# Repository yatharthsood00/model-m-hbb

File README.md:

# Model M Controller, by HBB

This is a drop-in replacement controller for the IBM Model M with QMK and VIAL support. I designed this for myself, and my own Models M, as well as some that I have sold/gifted to friends in the custom keyboard community, which is why this is designed only for the Models M that I own (the 101 key ANSI version, and the Space Saving Keyboard).

**Status (01-02-2026):** PCBA produced via JLCPCB and delivered. Tested successfully for basic operation. JST connector assembly in progress (I don't have a hot air soldering station).

## TODO:

1. Testing status lights and buzzer operation.
2. Uploading QMK and VIAL source to their respective repos.
3. BOM list availability in README (this file).
4. Fitment issue resolution due to USB-C port being too low for the existing cutout.
5. Figuring out solenoid operation and components required.
6. Pictures.

## Specs

- Based on the STM32F072CBT6 microcontroller, wide availability and great pedigree with QMK and VIAL. Works over USB-C.
- Like said, QMK and VIAL compatibility (firmware push and merge pending but it'll be there).
- Buzzer and Solenoid compatibility (optional, WIP). The exact parts needed for the solenoid are TBD and testing is required to be done first.
- Custom Status Lights PCB for adding LEDs in the colours of your choosing (standard DIP LEDs only), for the variants that have the possibility of adding such lights.
- Compatible with the 101-key and SSK Models M, Terminal or PS/2, both ANSI and ISO* versions.

*I need help with the firmware, as I don't own an ISO Model M to test it on.

## Why a new controller?

The "replacement Model M Controller" idea has already been implemented by many projects, with them already doing the work on understanding how the controller can be made in the first place, and the dimensions of a board that will fit the space voided by the original controller, that would be necessary to know how to place the components on my replacement. With that in mind, I would like to specifically highlight the [Ctrl-M](https://github.com/nuess0r/ctrl-M) and the [Model H](https://github.com/jhawthorn/modelh) projects, as they both provided me a sanity check of the dimensions of the PCB that I needed to design, separate from my own measurements of the several OEM controllers I now own.

While the above two are perfectly capable equivalents of my own creation, and I'm sure many would find either more suited for their own use cases, I found some limitations with the both of them that were disqualifying for my own use. Here is what I needed:

1. USB-C. All my other keyboards work off the same USB-C cable that I can detach from the keyboard end and swap the keyboard on my desk with another. While the Model H had this ability with the right Pro Micro controller, the Ctrl-M did not.
2. PCBA. It's significantly more expensive to produce this PCB via JLCPCB, with or without their assembly service. It's also almost conventional to expect a vintage keyboard replacement part to use a more "period-accurate" part selection, with through-hole componentry wherever possible, but I wanted something more modern that resembled a keyboard PCB you would get with a custom keyboard today. An entirely vain addition.
3. Additional bells and whistles. A keyboard with a solenoid is something I always wanted to add to my collection. While there are modern boards that will provide that to you, they are superseded, in my opinion, by a roomy plastic chassis, from a time when keyboards were normally significantly louer. Neither of the existing modules could provide that to me without a significant modification, so I decided to start from scratch.

Note: As a starting point for the solenoid and buzzer, I took directly from the [M122ion Control](https://github.com/dcpedit/mission-control) project, although the end result will use different components for the switching circuit.

All the above are fulfilled by this controller. This is also my first PCB design, and I enjoyed working on it. 

**As a disclaimer, however,** I don't claim this to be an extremely competent component, and I would advise anyone thinking of ordering a production run of this PCB to do their due diligence first. This is a hobbyist project first of all. Nonetheless, don't hesitate to reach out to me on @hardbodybrain on Discord, or on my personal email ID, yatharthsood00 [at] gmail [dot] com for any questions or clarifications, as well as if you want to share your experiences with this PCB, if you chose to get one of your own!

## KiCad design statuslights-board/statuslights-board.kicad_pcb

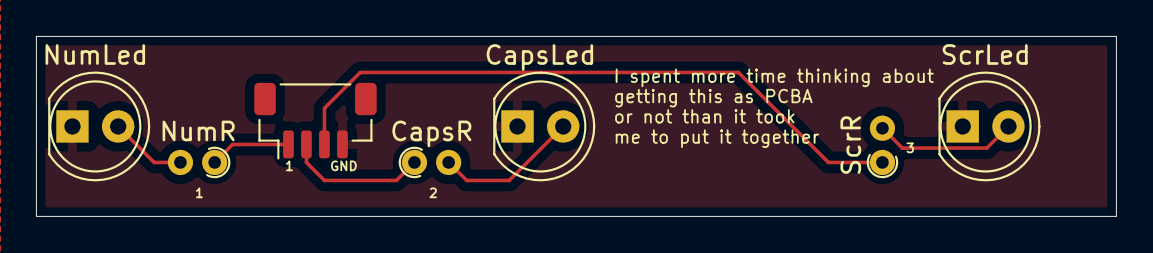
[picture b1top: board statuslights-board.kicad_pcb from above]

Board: 2 copper layers, 60.0 x 10.0 mm, 7 parts (0 on the bottom side), 7 nets.

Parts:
CapsLed: LED; LED_D5.0mm
CapsR: 51R; R_Axial_DIN0204_L3.6mm_D1.6mm_P1.90mm_Vertical
J1: JST SH (from controller); JST_SH_BM04B-SRSS-TB_1x04-1MP_P1.00mm_Vertical
NumLed: LED; LED_D5.0mm
NumR: 51R; R_Axial_DIN0204_L3.6mm_D1.6mm_P1.90mm_Vertical
ScrLed: LED; LED_D5.0mm
ScrR: 51R; R_Axial_DIN0204_L3.6mm_D1.6mm_P1.90mm_Vertical

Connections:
CapsLk: CapsR.1, J1.2
GND: CapsLed.1 (K), J1.4, NumLed.1 (K), ScrLed.1 (K)
unnamed: CapsLed.2 (A), CapsR.2
unnamed: NumLed.2 (A), NumR.2
unnamed: ScrLed.2 (A), ScrR.2
NumLk: J1.1, NumR.1
ScrLk: J1.3, ScrR.1

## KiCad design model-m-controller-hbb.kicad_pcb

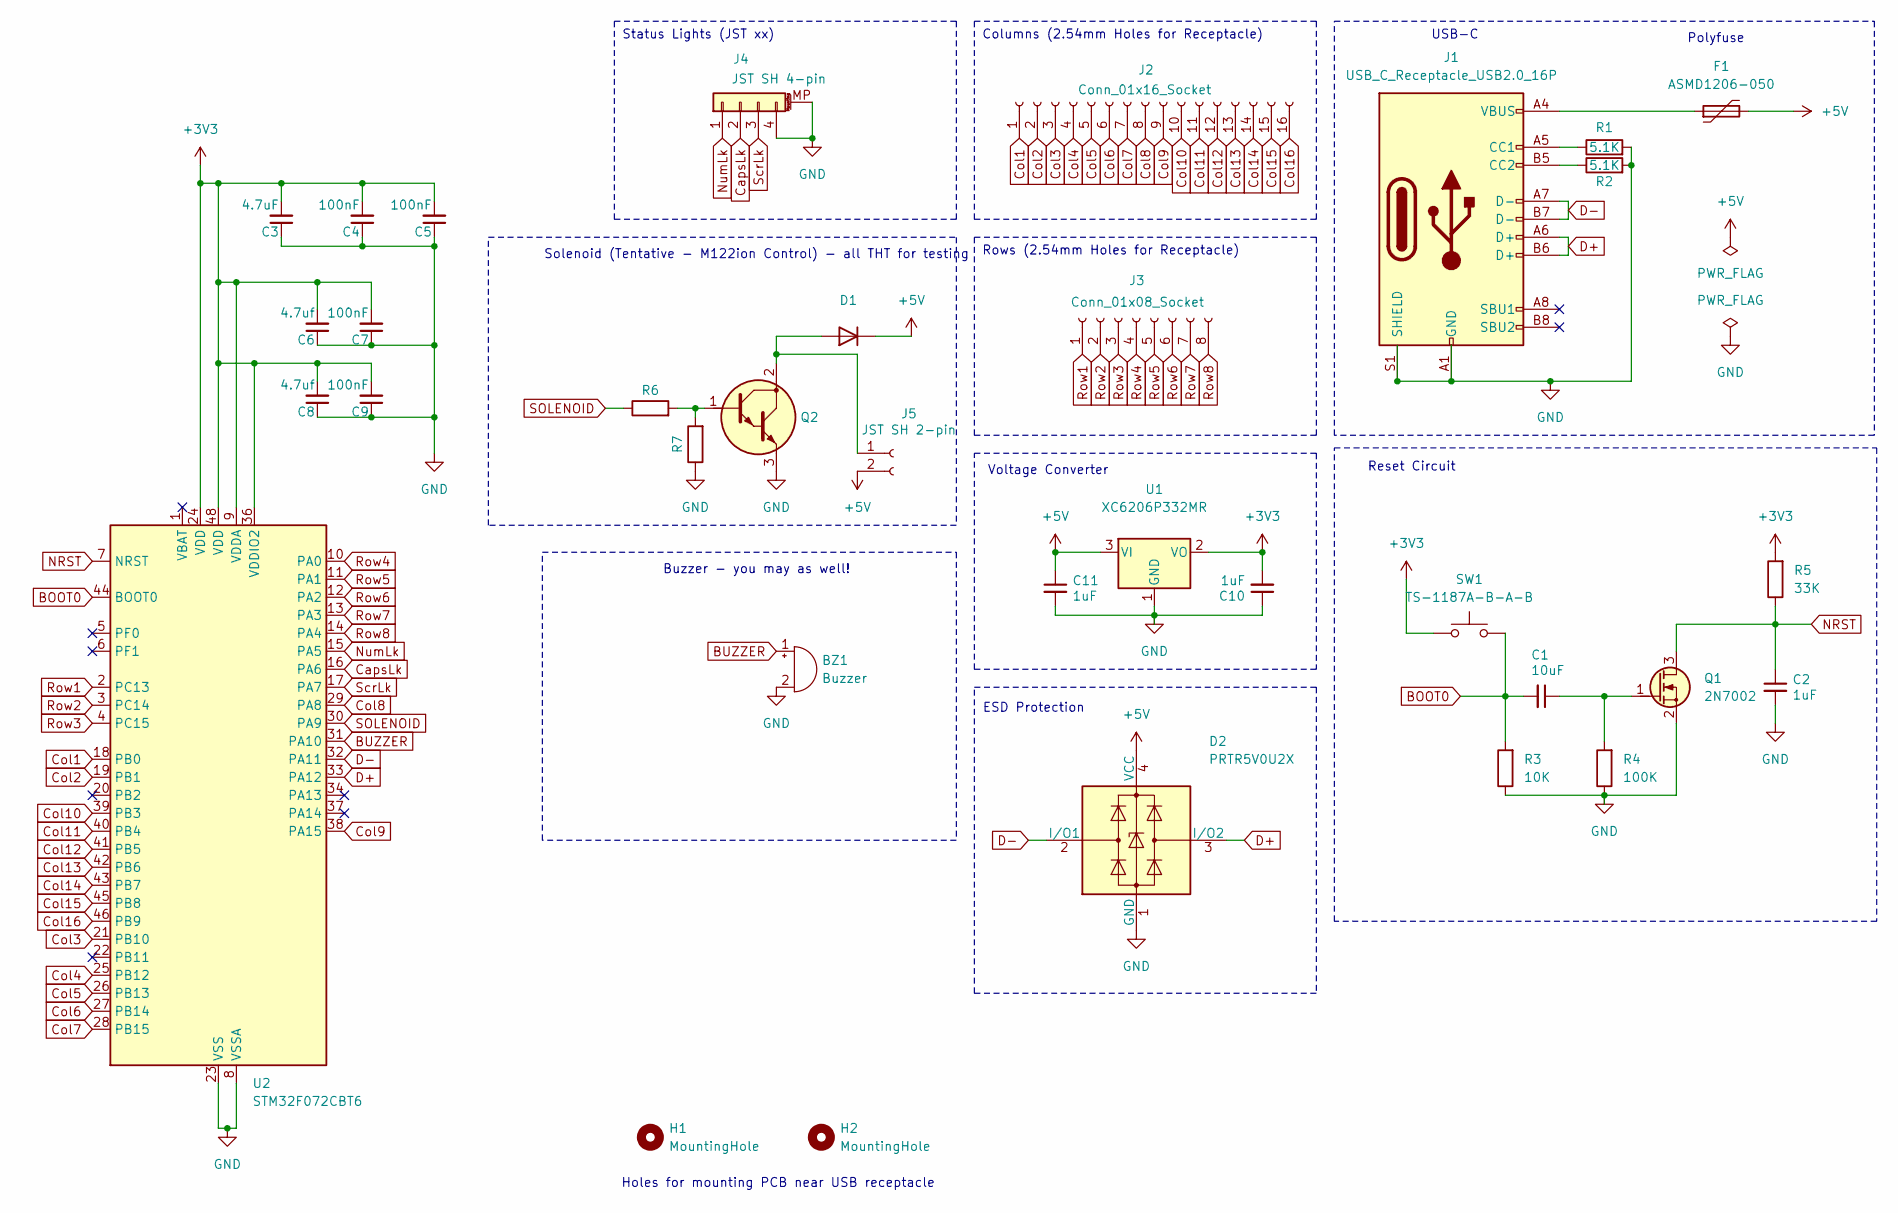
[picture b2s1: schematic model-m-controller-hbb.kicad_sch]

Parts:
BZ1: Buzzer; Buzzer_12x9.5RM7.6
C1: 10uF; C_0402_1005Metric; MPN CL05A105KA5NQNC; LCSC C52923
C2, C10, C11: 1uF; C_0402_1005Metric; MPN CL05A105KA5NQNC; LCSC C52923
C3: 4.7uF; C_0402_1005Metric
C4, C5, C7, C9: 100nF; C_0402_1005Metric
C6, C8: 4.7uf; C_0402_1005Metric
D1: D_DO-41_SOD81_P2.54mm_Vertical_AnodeUp
D2: PRTR5V0U2X; SOT-143; MPN PRTR5V0U2X
F1: ASMD1206-050; Fuse_1206_3216Metric
H1, H2: MountingHole; MountingHole_4mm
J1: USB_C_Receptacle_USB2.0_16P; USB_C_Receptacle_HRO_TYPE-C-31-M-12
J2: Conn_01x16_Socket; PinHeader_1x16_P2.54mm_Vertical
J3: Conn_01x08_Socket; PinHeader_1x08_P2.54mm_Vertical
J4: JST SH 4-pin; JST_SH_BM04B-SRSS-TB_1x04-1MP_P1.00mm_Vertical
J5: JST SH 2-pin; JST_SH_BM02B-SRSS-TB_1x02-1MP_P1.00mm_Vertical
Q1: 2N7002; SOT-23
Q2: TO-220-3_Vertical_BCE
R1, R2: 5.1K; R_0402_1005Metric
R3: 10K; R_0402_1005Metric
R4: 100K; R_0402_1005Metric
R5: 33K; R_0402_1005Metric
R6, R7: R_Axial_DIN0204_L3.6mm_D1.6mm_P1.90mm_Vertical
SW1: TS-1187A-B-A-B; SW_Push_1P1T_XKB_TS-1187A
U1: XC6206P332MR; SOT-23; MPN XC6206P332MR-G
U2: STM32F072CBT6; LQFP-48_7x7mm_P0.5mm

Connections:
+3V3: C3.2, C4.2, C5.2, C6.2, C7.2, C8.2, C9.2, C10.2, R5.2, SW1.1, U1.2 (VO), U2.9 (VDDA), U2.24 (VDD), U2.36 (VDDIO2), U2.48 (VDD)
+5V: C11.1, D1.1 (K), D2.4 (VCC), F1.2, J5.2, U1.3 (VI)
BOOT0: C1.2, R3.2, SW1.2, U2.44 (BOOT0)
BUZZER: BZ1.1 (+), U2.31 (PA10)
CapsLk: J4.2, U2.16 (PA6)
Col1: J2.1, U2.18 (PB0)
Col2: J2.2, U2.19 (PB1)
Col3: J2.3, U2.21 (PB10)
Col4: J2.4, U2.25 (PB12)
Col5: J2.5, U2.26 (PB13)
Col6: J2.6, U2.27 (PB14)
Col7: J2.7, U2.28 (PB15)
Col8: J2.8, U2.29 (PA8)
Col9: J2.9, U2.38 (PA15)
Col10: J2.10, U2.39 (PB3)
Col11: J2.11, U2.40 (PB4)
Col12: J2.12, U2.41 (PB5)
Col13: J2.13, U2.42 (PB6)
Col14: J2.14, U2.43 (PB7)
Col15: J2.15, U2.45 (PB8)
Col16: J2.16, U2.46 (PB9)
D+: D2.3 (I/O2), J1.A6 (D+), J1.B6 (D+), U2.33 (PA12)
D-: D2.2 (I/O1), J1.A7 (D-), J1.B7 (D-), U2.32 (PA11)
GND: BZ1.2 (-), C2.2, C3.1, C4.1, C5.1, C6.1, C7.1, C8.1, C9.1, C10.1, C11.2, D2.1 (GND), J1.A1 (GND), J1.A12 (GND), J1.B1 (GND), J1.B12 (GND), J1.S1 (SHIELD), J4.4, J4.MP (MountPin), Q1.2 (S), Q2.3 (E), R1.2, R2.2, R3.1, R4.1, R7.1, U1.1 (GND), U2.8 (VSSA), U2.23 (VSS), U2.35 (VSS), U2.47 (VSS)
NRST: C2.1, Q1.3 (D), R5.1, U2.7 (NRST)
unnamed: D1.2 (A), J5.1, Q2.2 (C)
unnamed: F1.1, J1.A4 (VBUS), J1.A9 (VBUS), J1.B4 (VBUS), J1.B9 (VBUS)
unnamed: J1.A5 (CC1), R1.1
unnamed: J1.B5 (CC2), R2.1
unnamed: C1.1, Q1.1 (G), R4.2
unnamed: Q2.1 (B), R6.2, R7.2
NumLk: J4.1, U2.15 (PA5)
Row1: J3.1, U2.2 (PC13)
Row2: J3.2, U2.3 (PC14)
Row3: J3.3, U2.4 (PC15)
Row4: J3.4, U2.10 (PA0)
Row5: J3.5, U2.11 (PA1)
Row6: J3.6, U2.12 (PA2)
Row7: J3.7, U2.13 (PA3)
Row8: J3.8, U2.14 (PA4)
SOLENOID: R6.1, U2.30 (PA9)
ScrLk: J4.3, U2.17 (PA7)

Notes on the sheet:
Columns (2.54mm Holes for Receptacle)
Status Lights (JST xx)
Rows (2.54mm Holes for Receptacle)
Holes for mounting PCB near USB receptacle
Polyfuse
Voltage Converter
ESD Protection
Reset Circuit
Solenoid (Tentative - M122ion Control) - all THT for testing
USB-C
Buzzer - you may as well!

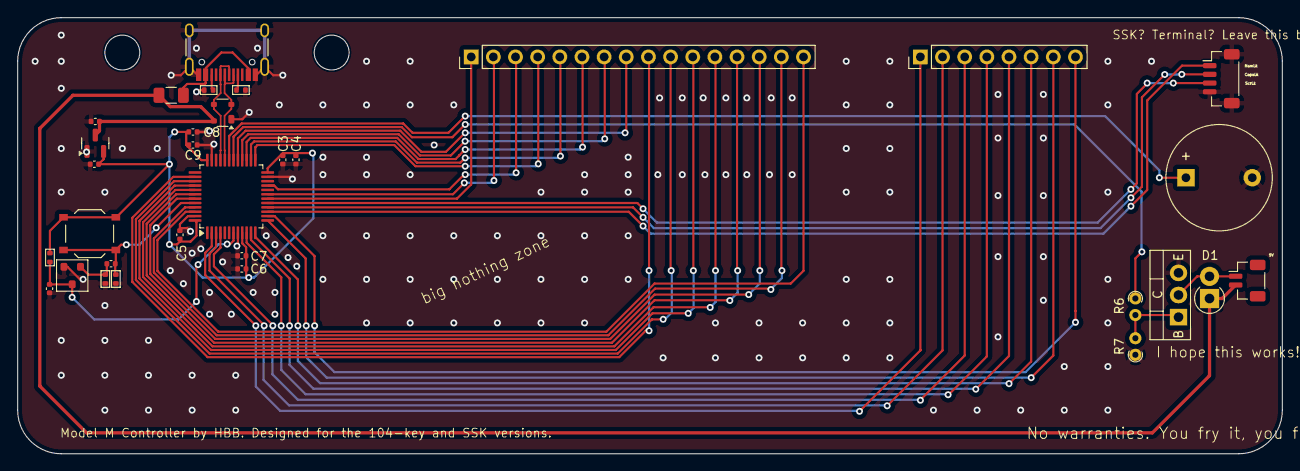
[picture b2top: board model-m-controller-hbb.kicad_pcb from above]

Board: 2 copper layers, 145.0 x 50.0 mm, 34 parts (0 on the bottom side), 42 nets.

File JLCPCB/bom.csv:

Designator,Footprint,Quantity,Value,LCSC Part #
BZ1,Buzzer_12x9.5RM7.6,1,Buzzer,
C1,0402,1,10uF,C52923
"C10, C11, C2",0402,3,1uF,C52923
"C3, C6, C8",0402,3,4.7uF,
"C4, C5, C7, C9",0402,4,100nF,
D1,D_DO-41_SOD81_P2.54mm_Vertical_AnodeUp,1,~,
D2,SOT-143,1,PRTR5V0U2X,
F1,1206,1,ASMD1206-050,
J1,USB_C_Receptacle_HRO_TYPE-C-31-M-12,1,USB_C_Receptacle_USB2.0_16P,
J2,PinHeader_1x16_P2.54mm_Vertical,1,Conn_01x16_Socket,
J3,PinHeader_1x08_P2.54mm_Vertical,1,Conn_01x08_Socket,
J4,JST_SH_BM04B-SRSS-TB_1x04-1MP_P1.00mm_Vertical,1,JST SH 4-pin,
J5,JST_SH_BM02B-SRSS-TB_1x02-1MP_P1.00mm_Vertical,1,JST SH 2-pin,
Q1,SOT-23,1,2N7002,
Q2,TO-220-3_Vertical_BCE,1,~,
"R1, R2",0402,2,5.1K,
R3,0402,1,10K,
R4,0402,1,100K,
R5,0402,1,33K,
"R6, R7",R_Axial_DIN0204_L3.6mm_D1.6mm_P1.90mm_Vertical,2,~,
SW1,SW_Push_1P1T_XKB_TS-1187A,1,TS-1187A-B-A-B,
U1,SOT-23,1,XC6206P332MR,
U2,LQFP-48_7x7mm_P0.5mm,1,STM32F072CBT6,

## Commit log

2026-02-01 Inital Commit, after v1 Production
2026-02-01 Added Status Lights files and project
2026-02-01 Added main and gerber README files
